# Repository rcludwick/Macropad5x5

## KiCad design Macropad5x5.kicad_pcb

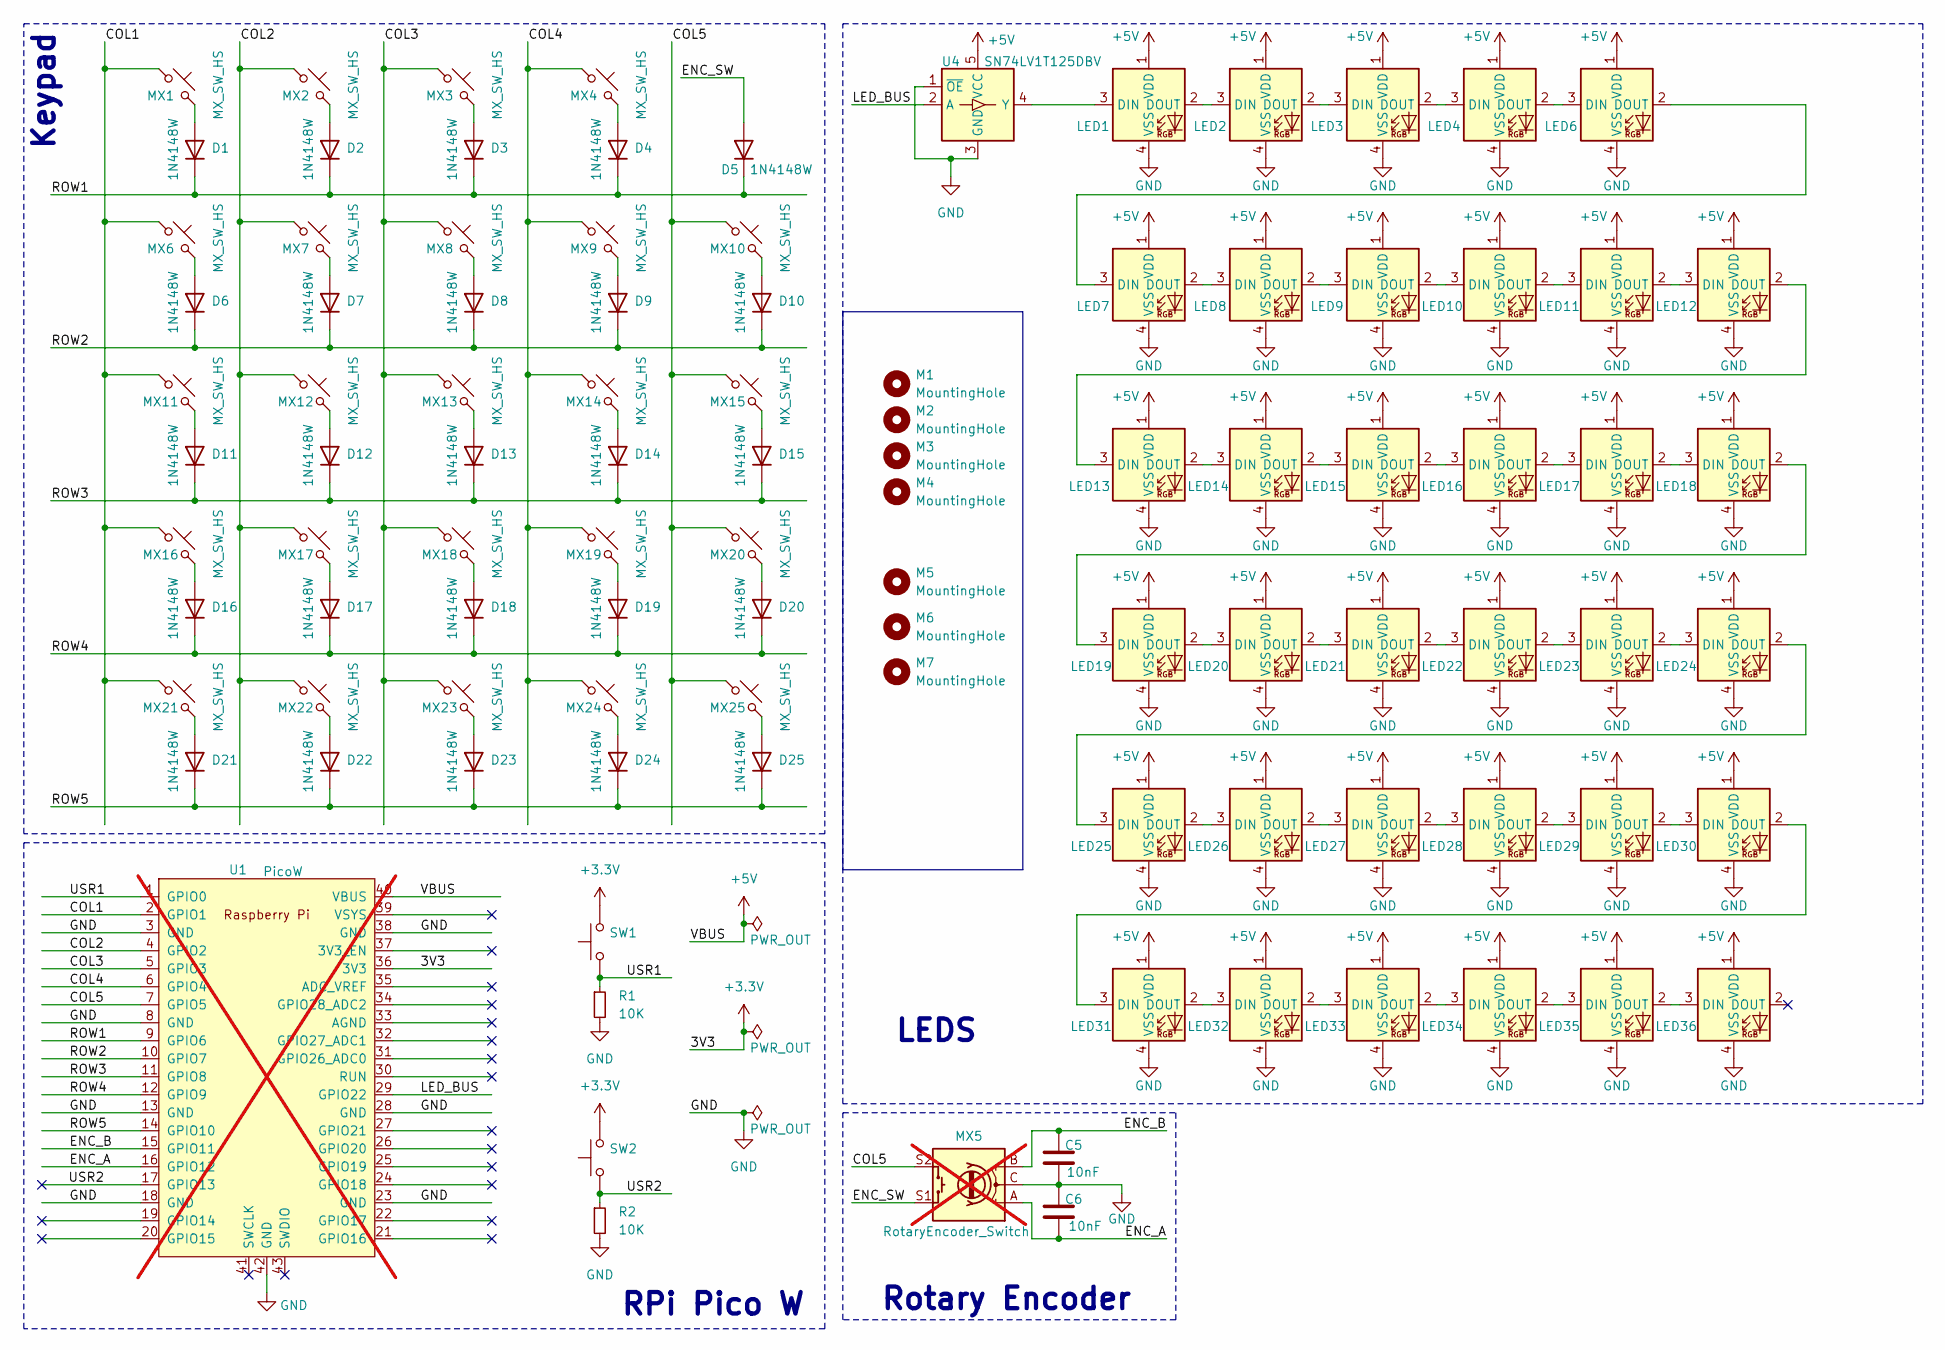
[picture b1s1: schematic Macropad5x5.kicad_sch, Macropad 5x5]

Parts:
C5, C6: 10nF; C_0805_2012Metric; LCSC C1710
D1, D2, D3, D4, D5, D6, D7, D8, D9, D10, D11, D12, D13, D14, D15, D16, D17, D18, D19, D20, D21, D22, D23, D24, D25: 1N4148W; D_SOD-123; LCSC C81598
LED1, LED2, LED3, LED4, LED6, LED7, LED8, LED9, LED10, LED11, LED12, LED13, LED14, LED15, LED16, LED17, LED18, LED19, LED20, LED21, LED22, LED23, LED24, LED25, LED26, LED27, LED28, LED29, LED30, LED31, LED32, LED33, LED34, LED35, LED36: choc_SK6812MINI-E; LED_choc_6028R; LCSC C5378731
M1, M2, M3, M4: MountingHole; MountingHole_3mm
M5, M6, M7: MountingHole; JLCPCB_Tooling_Hole
MX1, MX2, MX3, MX4, MX6, MX7, MX8, MX9, MX11, MX12, MX13, MX14, MX16, MX17, MX18, MX19, MX21, MX22, MX23, MX24: MX_SW_HS; SW_Cherry_MX_PCB_1.00u; LCSC C5156480
MX5: RotaryEncoder_Switch; RotaryEncoder_Alps_EC11E-Switch_Vertical_H20mm; not fitted
MX10, MX15, MX20, MX25: MX_SW_HS; SW_Cherry_MX_PCB_1.25u; LCSC C5156480
R1, R2: 10K; R_0805_2012Metric; LCSC C17414
SW1, SW2: SW_Push; SW_Push_1P1T_XKB_TS-1187A; LCSC C318884
U1: PicoW; RPi_PicoW_SMD_TH_NOSWD; not fitted
U4: SN74LV1T125DBV; SOT-23-5; LCSC C473338

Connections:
+3.3V: SW1.2, SW2.2, U1.36 (3V3)
+5V: LED1.1 (VDD), LED2.1 (VDD), LED3.1 (VDD), LED4.1 (VDD), LED6.1 (VDD), LED7.1 (VDD), LED8.1 (VDD), LED9.1 (VDD), LED10.1 (VDD), LED11.1 (VDD), LED12.1 (VDD), LED13.1 (VDD), LED14.1 (VDD), LED15.1 (VDD), LED16.1 (VDD), LED17.1 (VDD), LED18.1 (VDD), LED19.1 (VDD), LED20.1 (VDD), LED21.1 (VDD), LED22.1 (VDD), LED23.1 (VDD), LED24.1 (VDD), LED25.1 (VDD), LED26.1 (VDD), LED27.1 (VDD), LED28.1 (VDD), LED29.1 (VDD), LED30.1 (VDD), LED31.1 (VDD), LED32.1 (VDD), LED33.1 (VDD), LED34.1 (VDD), LED35.1 (VDD), LED36.1 (VDD), U1.40 (VBUS), U4.5 (VCC)
/COL1: MX1.1, MX6.1, MX11.1, MX16.1, MX21.1, U1.2 (GPIO1)
/COL2: MX2.1, MX7.1, MX12.1, MX17.1, MX22.1, U1.4 (GPIO2)
/COL3: MX3.1, MX8.1, MX13.1, MX18.1, MX23.1, U1.5 (GPIO3)
/COL4: MX4.1, MX9.1, MX14.1, MX19.1, MX24.1, U1.6 (GPIO4)
/COL5: MX5.S2, MX10.1, MX15.1, MX20.1, MX25.1, U1.7 (GPIO5)
/ENC_A: C6.2, MX5.A, U1.16 (GPIO12)
/ENC_B: C5.1, MX5.B, U1.15 (GPIO11)
/ENC_SW: D5.2 (A), MX5.S1
/LED_BUS: U1.29 (GPIO22), U4.2 (A)
/ROW1: D1.1 (K), D2.1 (K), D3.1 (K), D4.1 (K), D5.1 (K), U1.9 (GPIO6)
/ROW2: D6.1 (K), D7.1 (K), D8.1 (K), D9.1 (K), D10.1 (K), U1.10 (GPIO7)
/ROW3: D11.1 (K), D12.1 (K), D13.1 (K), D14.1 (K), D15.1 (K), U1.11 (GPIO8)
/ROW4: D16.1 (K), D17.1 (K), D18.1 (K), D19.1 (K), D20.1 (K), U1.12 (GPIO9)
/ROW5: D21.1 (K), D22.1 (K), D23.1 (K), D24.1 (K), D25.1 (K), U1.14 (GPIO10)
/USR1: R1.1, SW1.1, U1.1 (GPIO0)
/USR2: R2.1, SW2.1, U1.17 (GPIO13)
GND: C5.2, C6.1, LED1.4 (VSS), LED2.4 (VSS), LED3.4 (VSS), LED4.4 (VSS), LED6.4 (VSS), LED7.4 (VSS), LED8.4 (VSS), LED9.4 (VSS), LED10.4 (VSS), LED11.4 (VSS), LED12.4 (VSS), LED13.4 (VSS), LED14.4 (VSS), LED15.4 (VSS), LED16.4 (VSS), LED17.4 (VSS), LED18.4 (VSS), LED19.4 (VSS), LED20.4 (VSS), LED21.4 (VSS), LED22.4 (VSS), LED23.4 (VSS), LED24.4 (VSS), LED25.4 (VSS), LED26.4 (VSS), LED27.4 (VSS), LED28.4 (VSS), LED29.4 (VSS), LED30.4 (VSS), LED31.4 (VSS), LED32.4 (VSS), LED33.4 (VSS), LED34.4 (VSS), LED35.4 (VSS), LED36.4 (VSS), MX5.C, R1.2, R2.2, U1.3 (GND), U1.8 (GND), U1.13 (GND), U1.18 (GND), U1.23 (GND), U1.28 (GND), U1.38 (GND), U1.42 (GND), U4.1 (~OE), U4.3 (GND)
unnamed: D1.2 (A), MX1.2
unnamed: D2.2 (A), MX2.2
unnamed: D3.2 (A), MX3.2
unnamed: D4.2 (A), MX4.2
unnamed: D6.2 (A), MX6.2
unnamed: D7.2 (A), MX7.2
unnamed: D8.2 (A), MX8.2
unnamed: D9.2 (A), MX9.2
unnamed: D10.2 (A), MX10.2
unnamed: D11.2 (A), MX11.2
unnamed: D12.2 (A), MX12.2
unnamed: D13.2 (A), MX13.2
unnamed: D14.2 (A), MX14.2
unnamed: D15.2 (A), MX15.2
unnamed: D16.2 (A), MX16.2
unnamed: D17.2 (A), MX17.2
unnamed: D18.2 (A), MX18.2
unnamed: D19.2 (A), MX19.2
unnamed: D20.2 (A), MX20.2
unnamed: D21.2 (A), MX21.2
unnamed: D22.2 (A), MX22.2
unnamed: D23.2 (A), MX23.2
unnamed: D24.2 (A), MX24.2
unnamed: D25.2 (A), MX25.2
unnamed: LED1.3 (DIN), U4.4 (Y)
unnamed: LED1.2 (DOUT), LED2.3 (DIN)
unnamed: LED2.2 (DOUT), LED3.3 (DIN)
unnamed: LED3.2 (DOUT), LED4.3 (DIN)
unnamed: LED4.2 (DOUT), LED6.3 (DIN)
unnamed: LED6.2 (DOUT), LED7.3 (DIN)
unnamed: LED7.2 (DOUT), LED8.3 (DIN)
unnamed: LED8.2 (DOUT), LED9.3 (DIN)
unnamed: LED9.2 (DOUT), LED10.3 (DIN)
unnamed: LED10.2 (DOUT), LED11.3 (DIN)
unnamed: LED11.2 (DOUT), LED12.3 (DIN)
unnamed: LED12.2 (DOUT), LED13.3 (DIN)
unnamed: LED13.2 (DOUT), LED14.3 (DIN)
unnamed: LED14.2 (DOUT), LED15.3 (DIN)
unnamed: LED15.2 (DOUT), LED16.3 (DIN)
unnamed: LED16.2 (DOUT), LED17.3 (DIN)
unnamed: LED17.2 (DOUT), LED18.3 (DIN)
unnamed: LED18.2 (DOUT), LED19.3 (DIN)
unnamed: LED19.2 (DOUT), LED20.3 (DIN)
unnamed: LED20.2 (DOUT), LED21.3 (DIN)
unnamed: LED21.2 (DOUT), LED22.3 (DIN)
unnamed: LED22.2 (DOUT), LED23.3 (DIN)
unnamed: LED23.2 (DOUT), LED24.3 (DIN)
unnamed: LED24.2 (DOUT), LED25.3 (DIN)
unnamed: LED25.2 (DOUT), LED26.3 (DIN)
unnamed: LED26.2 (DOUT), LED27.3 (DIN)
unnamed: LED27.2 (DOUT), LED28.3 (DIN)
unnamed: LED28.2 (DOUT), LED29.3 (DIN)
unnamed: LED29.2 (DOUT), LED30.3 (DIN)
unnamed: LED30.2 (DOUT), LED31.3 (DIN)
unnamed: LED31.2 (DOUT), LED32.3 (DIN)
unnamed: LED32.2 (DOUT), LED33.3 (DIN)
unnamed: LED33.2 (DOUT), LED34.3 (DIN)
unnamed: LED34.2 (DOUT), LED35.3 (DIN)
unnamed: LED35.2 (DOUT), LED36.3 (DIN)

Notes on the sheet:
LEDS
Rotary Encoder
Keypad
RPi Pico W

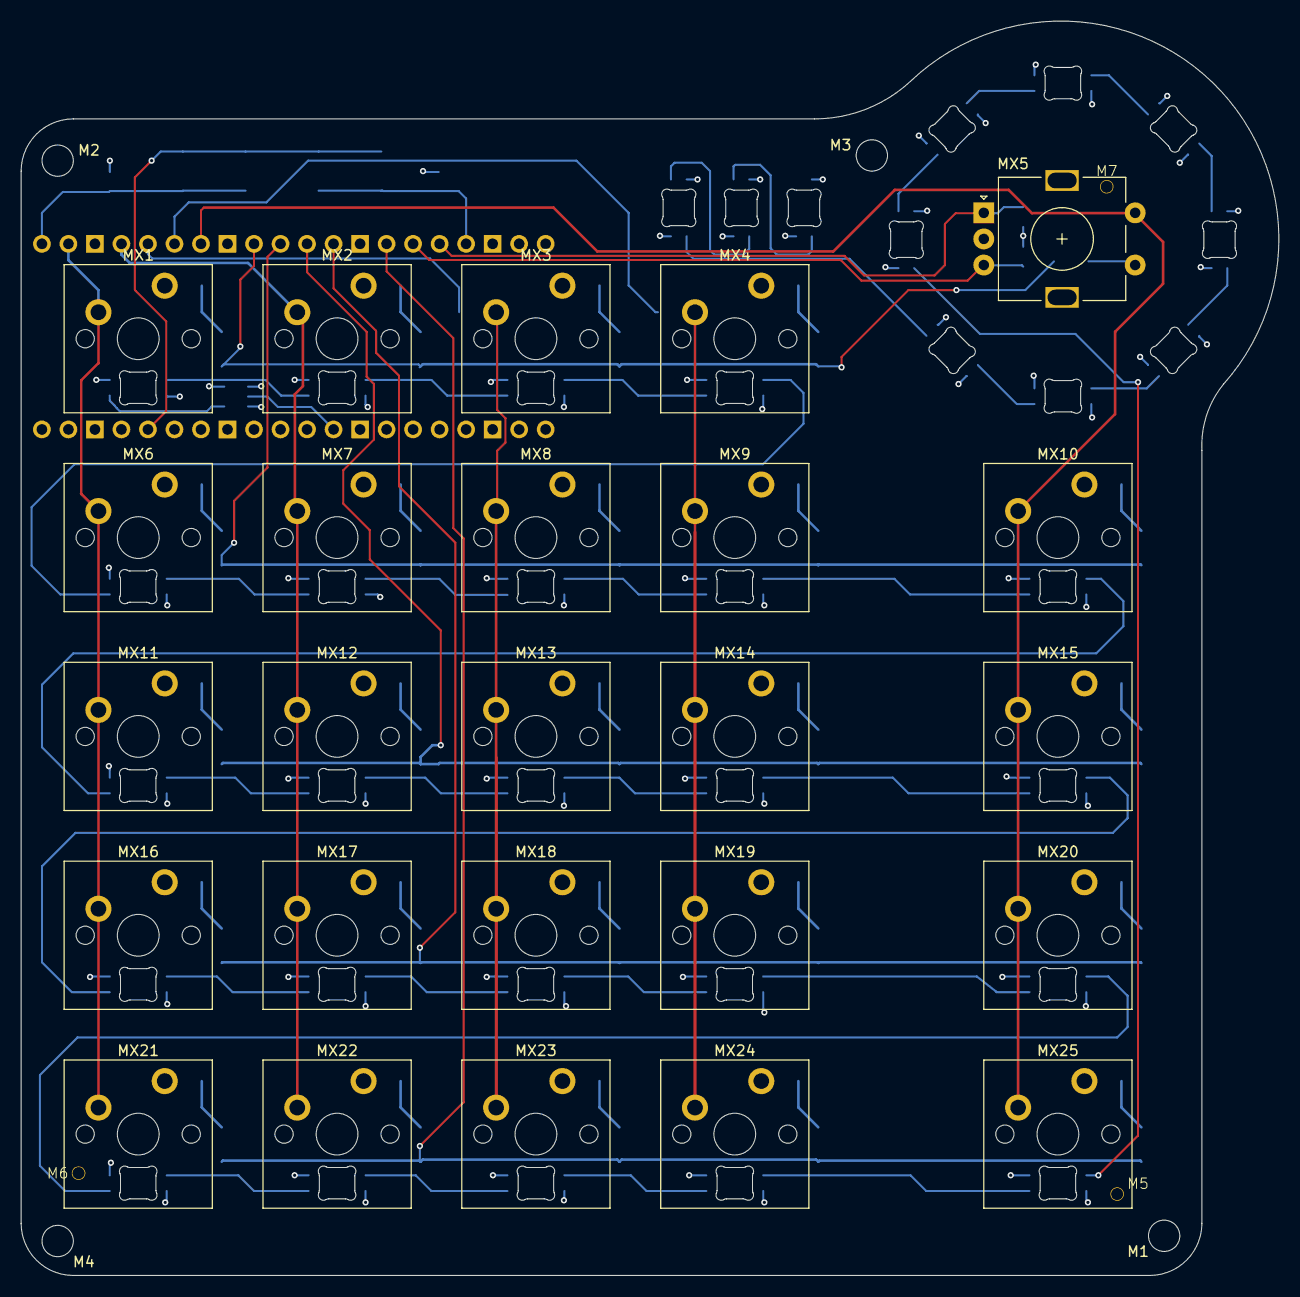
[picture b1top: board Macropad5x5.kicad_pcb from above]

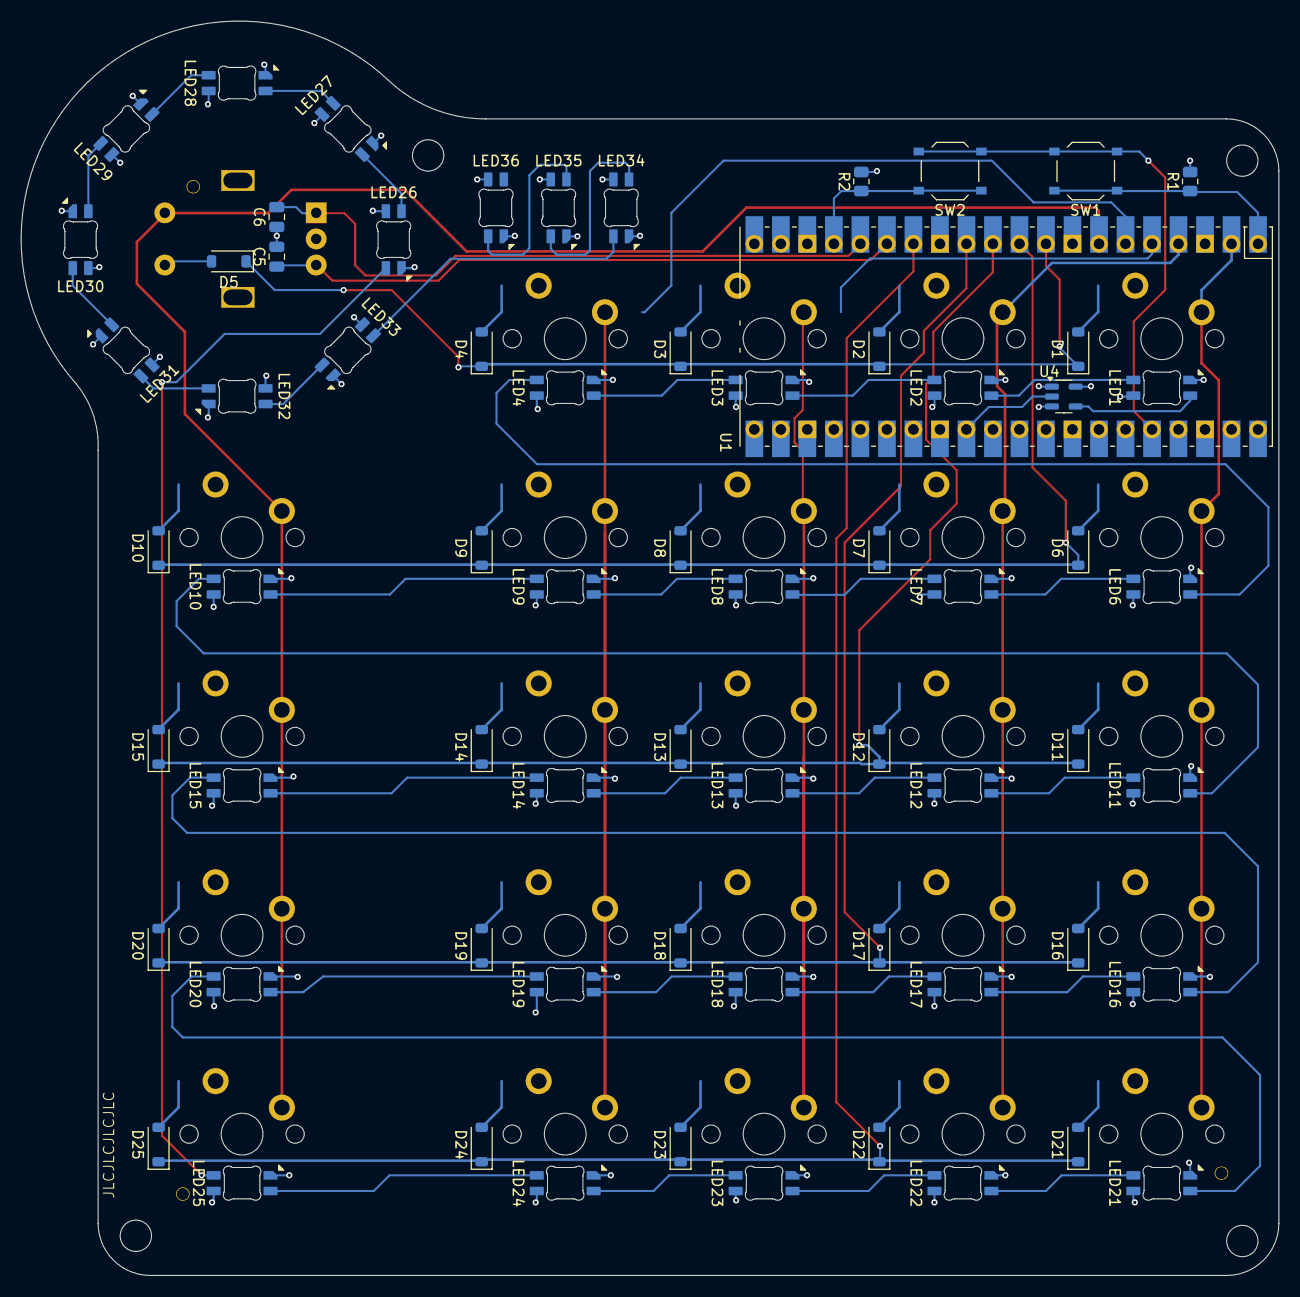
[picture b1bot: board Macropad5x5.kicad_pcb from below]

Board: 4 copper layers, 120.5 x 120.2 mm, 100 parts (68 on the bottom side), 78 nets.

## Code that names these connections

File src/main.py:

import network
from machine import Pin
import time

# Config file name:
WIFI_CONFIG_FILE = 'config.txt'
FALSE = ['0', "false", "False", "FALSE", False, None, "no", "No", "NO", "N"]
TRUE = ['1', "true", "True", "TRUE", True, "yes", "Yes", "YES", "Y"]

# Define row and column pin numbers for the 5x5 matrix
COLS = [1, 2, 3, 4, 5]
ROWS = [6, 7, 8, 9, 10]

# Initialize row and column pins
ROW_PINS = [Pin(row, Pin.OUT) for row in ROWS]
COL_PINS = [Pin(col, Pin.IN, Pin.PULL_UP) for col in COLS]

ENC_A = Pin(11, Pin.IN, Pin.PULL_UP)
ENC_B = Pin(12, Pin.IN, Pin.PULL_UP)

LED_BUS = 22
LED_PIN = Pin(LED_BUS, Pin.OUT)

#time.sleep(1)


def read_wifi_credentials_from_ini(file_path=WIFI_CONFIG_FILE):
    ssid = None
    password = None
    try:
        with open(file_path, 'r') as f:
            lines = f.readlines()
            for line in lines:
                if line.startswith('ssid='):
                    ssid = line.strip().split('=')[1]
                elif line.startswith('password='):
                    password = line.strip().split('=')[1]
                elif line.startswith('wifi_enabled'):
                    wifi_enabled = line.strip().split('=')[1]
                    if wifi_enabled in ['0', "false", "False", "FALSE"]:
                        return None, None
        return ssid, password
    except FileNotFoundError:
        return None, None


def scan_buttons():
    button_presses = []  # Store coordinates of pressed buttons as tuples (row, col)
    for row_index, row_pin in enumerate(ROW_PINS):
        row_pin.value(0)  # Activate row
        for col_index, col_pin in enumerate(COL_PINS):
            if not col_pin.value():  # Check if button is pressed
                button_presses.append((row_index, col_index))
        row_pin.value(1)  # Deactivate row

    # Check rotary encoder
    if not ENC_A.value():
        button_presses.append('ENC_A')
    if not ENC_B.value():
        button_presses.append('ENC_B')

    return button_presses

def connect_to_wifi(ssid, password):
    print("Connecting to WiFi...")
    wlan = network.WLAN(network.STA_IF)
    wlan.active(True)

    wlan.connect(ssid, password)
    while not wlan.isconnected():
        pass
    print("Connected to WiFi")
    return wlan


def main():
    # set the boot up neopixel to blue
    import neopixel
    array = neopixel.NeoPixel(LED_PIN, 35)
    array.fill((0, 0, 1))
    array.write()



    ssid, password = read_wifi_credentials_from_ini()
    if ssid and password:
        wlan = connect_to_wifi(ssid, password)


    while True:
        ...
        pressed_buttons = scan_buttons()
        if pressed_buttons:
            print("Buttons pressed:", pressed_buttons)

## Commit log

2024-07-22 Added keycaps 3d models
2024-07-22 Added step file for the macropad.
2024-07-22 Minor change to tracks.
2024-07-30 Updated 3d models.
2024-07-30 Updated schematic
2024-10-01 Updates and modifications
2024-10-01 Updates and modifications. Added 3d models

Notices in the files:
Macropad5x5.kicad_sch:
(c) 2024 Rob Ludwick
